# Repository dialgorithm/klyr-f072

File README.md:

<h1 align="center">
  klyr f072
  <br>
</h1>

<h4 align="center">
    STM32F072CBT6 dev board with usb c
</h4>

## Schematics + PCB

| Schematic | PCB |
|  |  |

| top layer | bottom layer |
|  |  |

## BOM

the complete bill of materials is available in [`bom.csv`](bom.csv).

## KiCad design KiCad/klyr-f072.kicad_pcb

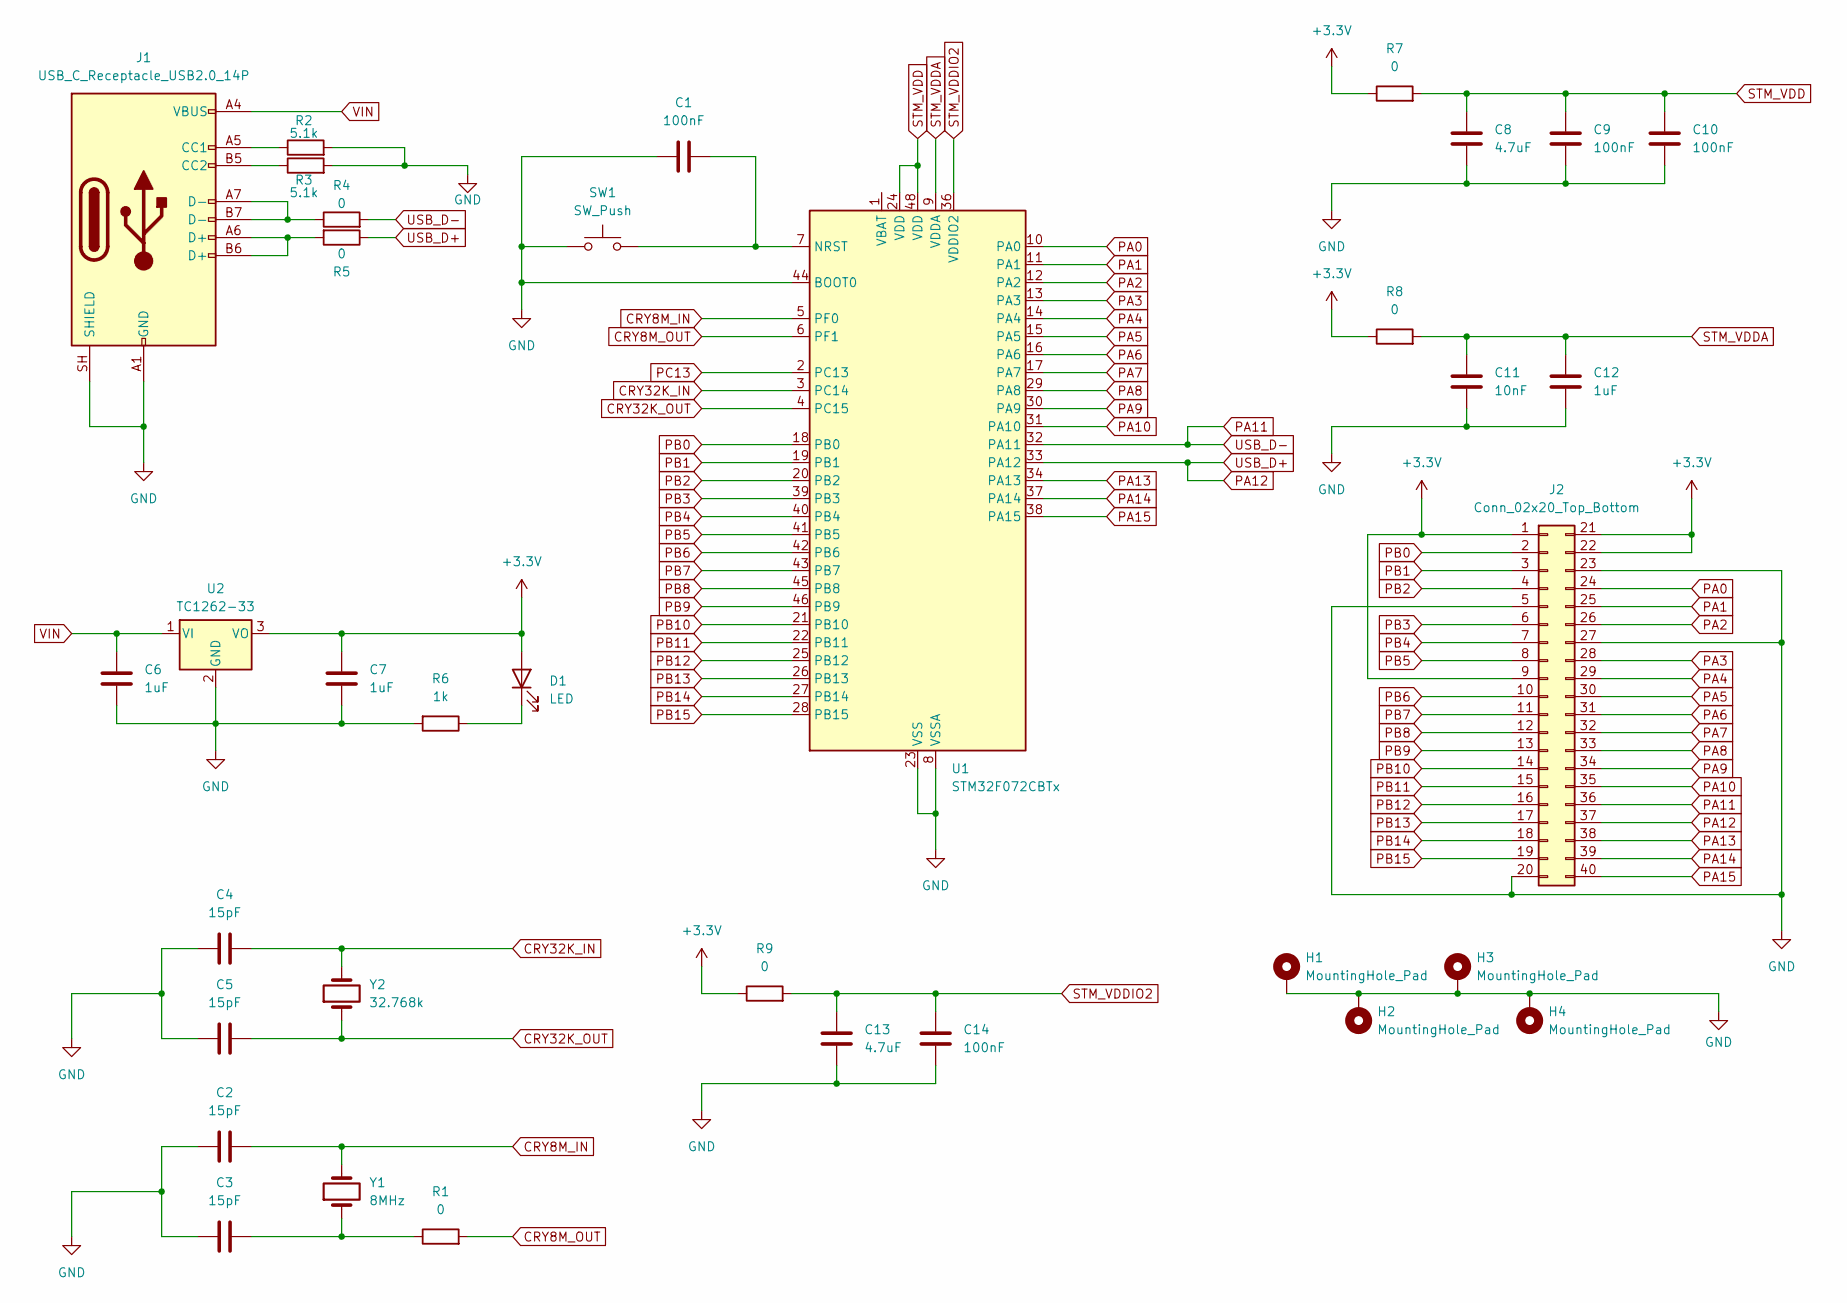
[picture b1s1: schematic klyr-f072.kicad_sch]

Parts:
C1, C9, C10, C14: 100nF; C_1206_3216Metric_Pad1.33x1.80mm_HandSolder
C2, C3, C4, C5: 15pF; C_1206_3216Metric_Pad1.33x1.80mm_HandSolder
C6, C7, C12: 1uF; C_1206_3216Metric_Pad1.33x1.80mm_HandSolder
C8, C13: 4.7uF; C_1206_3216Metric_Pad1.33x1.80mm_HandSolder
C11: 10nF; C_1206_3216Metric_Pad1.33x1.80mm_HandSolder
D1: LED; LED_1206_3216Metric_Pad1.42x1.75mm_HandSolder
H1, H2, H3, H4: MountingHole_Pad; MountingHole_2.7mm_M2.5_DIN965_Pad
J1: USB_C_Receptacle_USB2.0_14P; USB_C_Receptacle_HRO_TYPE-C-31-M-12
J2: Conn_02x20_Top_Bottom; PinHeader_2x20_P2.54mm_Vertical
R1, R4, R5, R7, R8, R9: 0; R_1206_3216Metric_Pad1.30x1.75mm_HandSolder
R2, R3: 5.1k; R_1206_3216Metric_Pad1.30x1.75mm_HandSolder
R6: 1k; R_1206_3216Metric_Pad1.30x1.75mm_HandSolder
SW1: SW_Push; SW_Push_1P1T_NO_E-Switch_TL3301NxxxxxG
U1: STM32F072CBTx; LQFP-48_7x7mm_P0.5mm
U2: TC1262-33; SOT-223-3_TabPin2
Y1: 8MHz; Crystal_HC49-U_Vertical
Y2: 32.768k; Crystal_SMD_3215-2Pin_3.2x1.5mm

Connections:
+3.3V: C7.1, D1.2 (A), J2.1, J2.9, J2.21, J2.22, R7.1, R8.1, R9.1, U2.3 (VO)
CRY8M_IN: C2.2, U1.5 (PF0), Y1.2
CRY8M_OUT: R1.2, U1.6 (PF1)
CRY32K_IN: C4.2, U1.3 (PC14), Y2.2
CRY32K_OUT: C5.2, U1.4 (PC15), Y2.1
GND: C1.1, C2.1, C3.1, C4.1, C5.1, C6.2, C7.2, C8.2, C9.2, C10.2, C11.2, C12.2, C13.2, C14.2, H1.1 (1_1), H2.1 (1_1), H3.1 (1_1), H4.1 (1_1), J1.A1 (GND), J1.A12 (GND), J1.B1 (GND), J1.B12 (GND), J1.SH (SHIELD), J2.5, J2.20, J2.23, J2.27, R2.2, R3.2, R6.2, SW1.1, U1.8 (VSSA), U1.23 (VSS), U1.35 (VSS), U1.44 (BOOT0), U1.47 (VSS), U2.2 (GND)
unnamed: C3.2, R1.1, Y1.1
unnamed: D1.1 (K), R6.1
unnamed: J1.A5 (CC1), R2.1
unnamed: J1.B5 (CC2), R3.1
unnamed: J1.A6 (D+), J1.B6 (D+), R5.2
unnamed: J1.A7 (D-), J1.B7 (D-), R4.1
unnamed: C1.2, SW1.2, U1.7 (NRST)
PA0: J2.24, U1.10 (PA0)
PA1: J2.25, U1.11 (PA1)
PA2: J2.26, U1.12 (PA2)
PA3: J2.28, U1.13 (PA3)
PA4: J2.29, U1.14 (PA4)
PA5: J2.30, U1.15 (PA5)
PA6: J2.31, U1.16 (PA6)
PA7: J2.32, U1.17 (PA7)
PA8: J2.33, U1.29 (PA8)
PA9: J2.34, U1.30 (PA9)
PA10: J2.35, U1.31 (PA10)
PA11: J2.36, R4.2, U1.32 (PA11)
PA12: J2.37, R5.1, U1.33 (PA12)
PA13: J2.38, U1.34 (PA13)
PA14: J2.39, U1.37 (PA14)
PA15: J2.40, U1.38 (PA15)
PB0: J2.2, U1.18 (PB0)
PB1: J2.3, U1.19 (PB1)
PB2: J2.4, U1.20 (PB2)
PB3: J2.6, U1.39 (PB3)
PB4: J2.7, U1.40 (PB4)
PB5: J2.8, U1.41 (PB5)
PB6: J2.10, U1.42 (PB6)
PB7: J2.11, U1.43 (PB7)
PB8: J2.12, U1.45 (PB8)
PB9: J2.13, U1.46 (PB9)
PB10: J2.14, U1.21 (PB10)
PB11: J2.15, U1.22 (PB11)
PB12: J2.16, U1.25 (PB12)
PB13: J2.17, U1.26 (PB13)
PB14: J2.18, U1.27 (PB14)
PB15: J2.19, U1.28 (PB15)
PC13: U1.2 (PC13)
STM_VDD: C8.1, C9.1, C10.1, R7.2, U1.24 (VDD), U1.48 (VDD)
STM_VDDA: C11.1, C12.1, R8.2, U1.9 (VDDA)
STM_VDDIO2: C13.1, C14.1, R9.2, U1.36 (VDDIO2)
VIN: C6.1, J1.A4 (VBUS), J1.A9 (VBUS), J1.B4 (VBUS), J1.B9 (VBUS), U2.1 (VI)

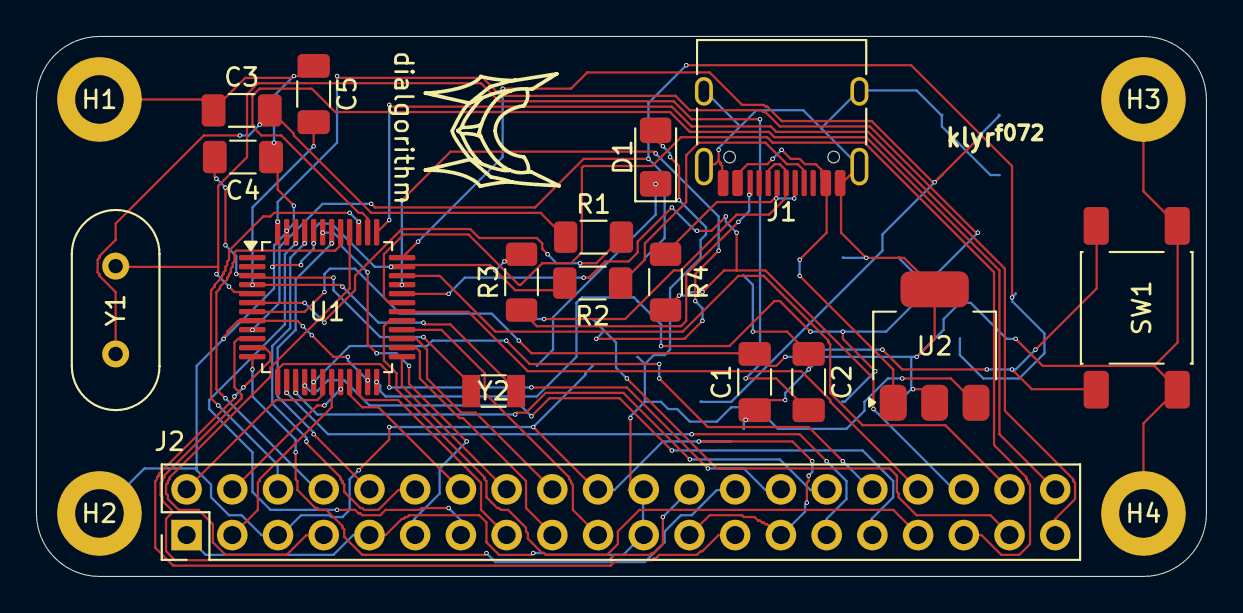
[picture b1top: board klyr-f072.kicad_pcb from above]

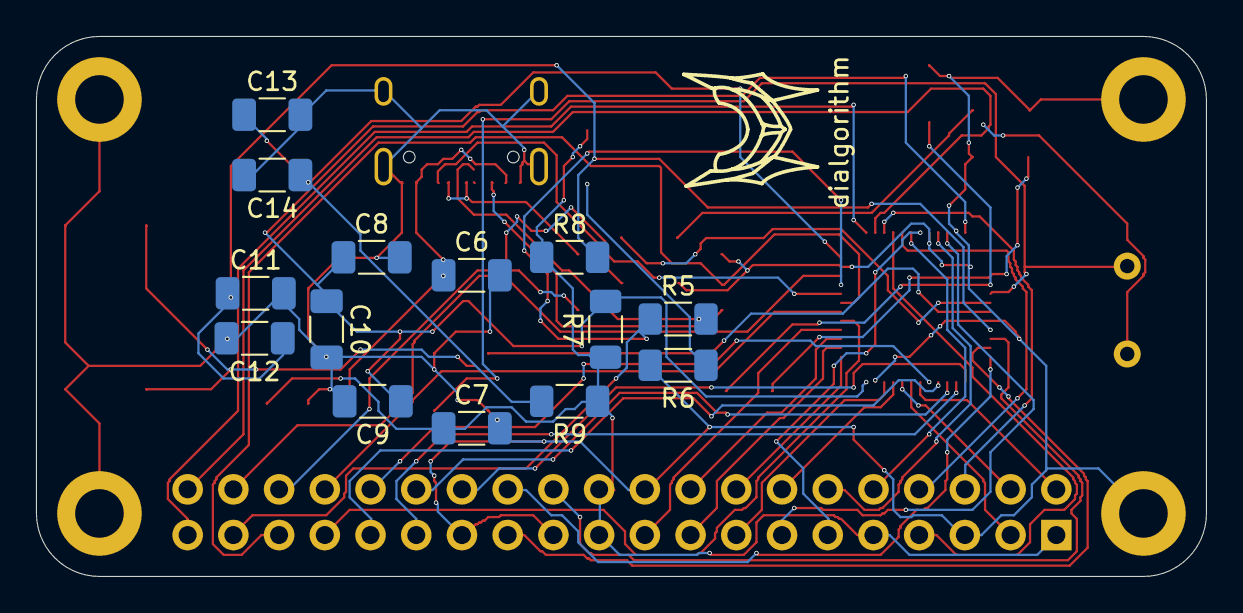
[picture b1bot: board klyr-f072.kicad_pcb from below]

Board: 2 copper layers, 65.0 x 30.0 mm, 37 parts (15 on the bottom side), 49 nets.

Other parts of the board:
dialgorithm: dialgorithm
dialgorithm#2: dialgorithm
